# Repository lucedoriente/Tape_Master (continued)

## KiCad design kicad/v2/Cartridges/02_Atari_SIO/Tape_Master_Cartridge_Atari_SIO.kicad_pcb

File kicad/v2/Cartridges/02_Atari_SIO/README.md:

# Tape Master v2 — Cartuccia 02: Atari 8-Bit SIO Tape Interface

| Proprietà | Dettaglio / Valore |
| :--- | :--- |
| **Progetto** | Tape Master Exerciser & Signal Digitizer v2 |
| **Modulo** | Cartuccia Espansione #02 — Atari SIO (`02_Atari_SIO`) |
| **Piattaforme Compatibili** | Atari 400, 800, 800XL, 65XE, 130XE, XEGS, XE Game System |
| **Periferiche Supportate** | Atari 410, 1010, XC11, XC12, CA-12, XCA12, XC13, registratori compatibili Turbo (KSO, Silesia, Turbo 2000) |
| **Autore & Hardware Designer** | Alessio Iodice (`alessio67@gmail.com`) |
| **Data di Rilascio** | 2026-11-06 |
| **Revisione** | 2.0 (KiCad 9.0 Nativo) |
| **Licenza** | CC BY-NC-SA 4.0 |
| **Stato Validazione KiCad 9** | **0 Violazioni ERC / 0 Violazioni DRC / 0 Net Non Connesse / 0 Parity Issues** |

---

## 1. Descrizione Architetturale

La cartuccia **Cartuccia 02: Atari SIO** interfaccia il sistema **Tape Master v2** al bus seriale proprietario **Atari SIO (Serial Input/Output)** a 13 pin, utilizzato dall'intera famiglia di personal computer a 8-bit Atari (400, 800, serie XL, serie XE) per il pilotaggio dei registratori a cassette (modelli 410, 1010, XC11, XC12 e derivati con turbo tape).

### Caratteristiche Elettriche Chiave
1. **Trasmissione Dati Asincrona SIO (DATA IN - Pin 3)**:
   - La linea `DATA IN` dell'Atari opera a 600 baud (standard Atari FSK audio demodulato) o a bitrate superiori (sistemi Turbo fino a $4800\text{ baud}$).
   - Pilotata tramite doppio stadio invertitore Open-Collector ad alta velocità **74HCT06** (`U2`), con resistenza di pull-up locale da $1\text{ k}\Omega$ verso `+5V_SIO` (host console) e resistenza di pull-up da $10\text{ k}\Omega$ sull'ingresso logico collegato alla Mainboard.
2. **Ricezione Dati (DATA OUT - Pin 5)**:
   - Traslazione di livello da 5V a 3.0V tramite partitore resistivo di precisione ($R_1 = 2.2\text{ k}\Omega$, $R_2 = 3.3\text{ k}\Omega$) con clamp a doppio diodo Schottky a commutazione ultra-rapida **BAT54S** (`D2`) verso `+3.3V` e `GND`, proteggendo l'ingresso MCU `TAPE_REC_IN`.
3. **Controllo & Rilevamento Motore (MOTOR - Pin 8)**:
   - L'Atari attiva il motore tirando la linea a livello logico basso / massa (transistor open-collector sul computer).
   - Resistenza di pull-up da $10\text{ k}\Omega$ (`R3`) verso `+5V_SIO`, partitore $2.2\text{ k}\Omega / 3.3\text{ k}\Omega$ (`R4`, `R5`) e clamp Schottky **BAT54S** (`D4`) verso la linea `MOTOR_SENSE` della scheda madre.
4. **Acquisizione Audio / Traccia Stereo Ingest (AUDIO IN - Pin 11)**:
   - Il bus SIO prevede sul Pin 11 una traccia audio ausiliaria (usata nei nastri didattici Atari per audio parlato o musica mentre la traccia dati viene caricata in RAM).
   - Circuito di condizionamento dedicato con condensatore di disaccoppiamento DC da $4.7\ \mu\text{F}$ (`C3`), filtro passa-basso RC passivo ($R_6 = 1\text{ k}\Omega$, $C_4 = 10\text{ nF}$, frequenza di taglio $f_c \approx 15.9\text{ kHz}$) e resistenza di carico shunt da $10\text{ k}\Omega$ (`R7`), inviata alla linea `AUDIO_RAW_L` per il campionamento ADC / digitalizzazione stereo.
5. **Protezione ESD / Transitori**:
   - Array di soppressione TVS a bassa capacità parassita **USBLC6-2SC6** (`D1`) su tutte e 4 le linee esposte (`SIO_DATA_IN`, `SIO_DATA_OUT`, `SIO_MOTOR`, `SIO_AUDIO_IN`).
6. **Smart Plug & Play (Auto-ID Cartridge)**:
   - EEPROM I2C **24C02** (`U1`) configurata all'indirizzo `0x51` (`A0=1, A1=0, A2=0`), contenente il descrittore hardware con magic byte, revisione, pinout e parametri di campionamento.
   - Pin 26 del connettore bus principale `CART_DETECT_N` collegato a massa per rilevamento hardware automatico dell'inserimento scheda.
7. **Monitor Alimentazione Atari Console**:
   - Micro-LED verde 0805 `D3` (`+5V_SIO_OK`) con resistenza di zavorra da $1.5\text{ k}\Omega$ (`R10`), unico LED ammesso sulla cartuccia come da regole di progetto per visualizzare a colpo d'occhio la presenza dell'alimentazione erogata dalla console vintage.

---

## 2. Centralizzazione Diagnostica sul Front Panel (Daughterboard)

Come prescritto dalle regole ufficiali di progetto `tape-master-rules.md`, l'intera interfaccia diagnostica e di stato per l'operatore è centralizzata sul pannello frontale (`Tape_Master_UI_Panel`), evitando LED duplicati non visibili a banco.

I 5 LED diagnostici standardizzati sul pannello operatore riflettono il funzionamento della cartuccia Atari SIO:

| Riferimento UI | Colore | Serigrafia Standard | Segnale Mappato per Atari SIO | Funzione Operativa |
| :---: | :---: | :---: | :--- | :--- |
| **D2** | Verde | **`PLAY`** | `SIO_DATA_IN` (Pin 3) | Trasmissione dati dal Tape Master verso la console Atari (emulazione nastro CAS / dump) |
| **D3** | Rosso | **`REC`** | `SIO_DATA_OUT` (Pin 5) | Ricezione dati e salvataggio dump dal computer Atari verso il Tape Master |
| **D4** | Giallo | **`MOTOR`** | `SIO_MOTOR` (Pin 8) | Linea motore abilitata dall'Atari (computer in attesa di caricamento o salvataggio) |
| **D5** | Blu | **`SIGNAL`** | `SIO_AUDIO_IN` (Pin 11) | Presenza traccia audio analogica / sincronismo portante SIO / turbo pulse |
| **D6** | Verde | **`PWR`** | Alimentazione Tape Master | Alimentazione principale di sistema attiva e MCU operativo |
| **D10..D19** | 8V/1G/1R | **`AZIMUTH / VU-METER`** | Livello di picco ADC `AUDIO_RAW_L` | Barra VU-meter per regolazione azimut / livello volume traccia parlato |

---

## 3. Doppia Connettività Esterna

La cartuccia adotta la configurazione a **doppia porta**:
1. **`J2` — Presa Femmina Proprietaria Atari SIO 13-Pin**: Connettore a guscio originale per l'inserimento diretto del cavo SIO standard proveniente dal computer o dal registratore.
2. **`J3` — Pin-Header Maschio Breakout 1x13 passo 2.54 mm**: Pin header montato a bordo scheda con serigrafia esplicita di ciascun pin, ideale per test a banco, oscilloscopio, analizzatore logico o cablaggi rapidi.

### Piedinatura Connettori SIO (`J2` e `J3`)

| Pin # | Segnale SIO | Connessione su Cartuccia | Direzione | Descrizione |
| :---: | :--- | :--- | :---: | :--- |
| **1** | `CLK_I` (Clock In) | Header Breakout `J3` / `J2` | Ingresso Atari | Segnale di clock esterno per periferiche sincrone |
| **2** | `CLK_O` (Clock Out) | Header Breakout `J3` / `J2` | Uscita Atari | Clock generato dalla CPU/POKEY |
| **3** | `DATA_IN` | Buffer Open-Collector `74HCT06` | Ingresso Atari | Ricezione seriale dati dal registratore (600+ baud) |
| **4** | `GND` | Piano di Massa Scheda (`GND`) | Riferimento | Massa logica e potenza |
| **5** | `DATA_OUT` | Partitore $2.2\text{k}/3.3\text{k}$ $\rightarrow$ `TAPE_REC_IN` | Uscita Atari | Dati seriali trasmessi dalla console verso la cassetta |
| **6** | `GND` | Piano di Massa Scheda (`GND`) | Riferimento | Massa logica e potenza |
| **7** | `COMMAND` | Pull-up $10\text{ k}\Omega$ $\rightarrow$ Header Breakout `J3` | Uscita Atari | Linea di comando attiva bassa (abilitazione bus per disk drive) |
| **8** | `MOTOR` | Pull-up + Partitore $\rightarrow$ `MOTOR_SENSE` | Uscita Atari | Controllo motore registratore (attivo a 0V) |
| **9** | `PROCEED` | Header Breakout `J3` / `J2` | Ingresso Atari | Linea di interrupt / handshake periferiche |
| **10** | `+5V_SIO` | Monitor LED `D3` & Pull-up buffer | Uscita Atari | Tensione +5V erogata dall'Atari (max $100\text{ mA}$) |
| **11** | `AUDIO_IN` | Filtro passa-basso $15.9\text{ kHz}$ $\rightarrow$ `AUDIO_RAW_L` | Ingresso Atari | Traccia audio analogica ausiliaria cassetta |
| **12** | `+12V` | Header Breakout `J3` / `J2` | Non connesso | Presente solo su Atari 400/800 per alimentatori d'epoca |
| **13** | `INTERRUPT` | Header Breakout `J3` / `J2` | Ingresso Atari | Linea di richiesta interruzione al computer |

---

## 4. Specifiche Meccaniche e Bordo Scheda

- **Dimensioni**: $74.00\text{ mm} \times 55.00\text{ mm}$.
- **Intagli Meccanici**: Due intagli su `Edge.Cuts` ($6.0\text{ mm} \times 8.0\text{ mm}$) per l'alloggiamento delle leve di ritenuta del connettore `J1` della Mainboard.
- **Complanarità**: Connettore maschio ad angolo retto sulla Mainboard e connettore femmina ad angolo retto sulla Cartuccia (`J1`) permettono alle due schede di rimanere **perfettamente parallele e complanari**, con la cartuccia che estende orizzontalmente all'indietro il corpo principale del Tape Master.

---

## 5. File di Rilascio e Produzione

- Schema Elettrico KiCad: `Tape_Master_Cartridge_Atari_SIO.kicad_sch`
- Layout PCB KiCad: `Tape_Master_Cartridge_Atari_SIO.kicad_pcb`
- Modello 3D Meccanico Solido PCB Assemblato: `Tape_Master_Cartridge_Atari_SIO.step`
- Schema Elettrico Vettoriale: `Tape_Master_Cartridge_Atari_SIO.pdf` e `Tape_Master_Cartridge_Atari_SIO_Sch.svg`
- Disegno PCB Top Layer: `Tape_Master_Cartridge_Atari_SIO_Top.pdf` e `Tape_Master_Cartridge_Atari_SIO_Top.svg`
- Disegno PCB Bottom Layer: `Tape_Master_Cartridge_Atari_SIO_Bottom.pdf`
- Report Collaudo ERC: `Tape_Master_Cartridge_Atari_SIO-erc.rpt` (0 errori, 0 warning)
- Report Collaudo DRC: `Tape_Master_Cartridge_Atari_SIO-drc.rpt` (0 errori, 0 warning, 0 unconnected, 0 parity issues)

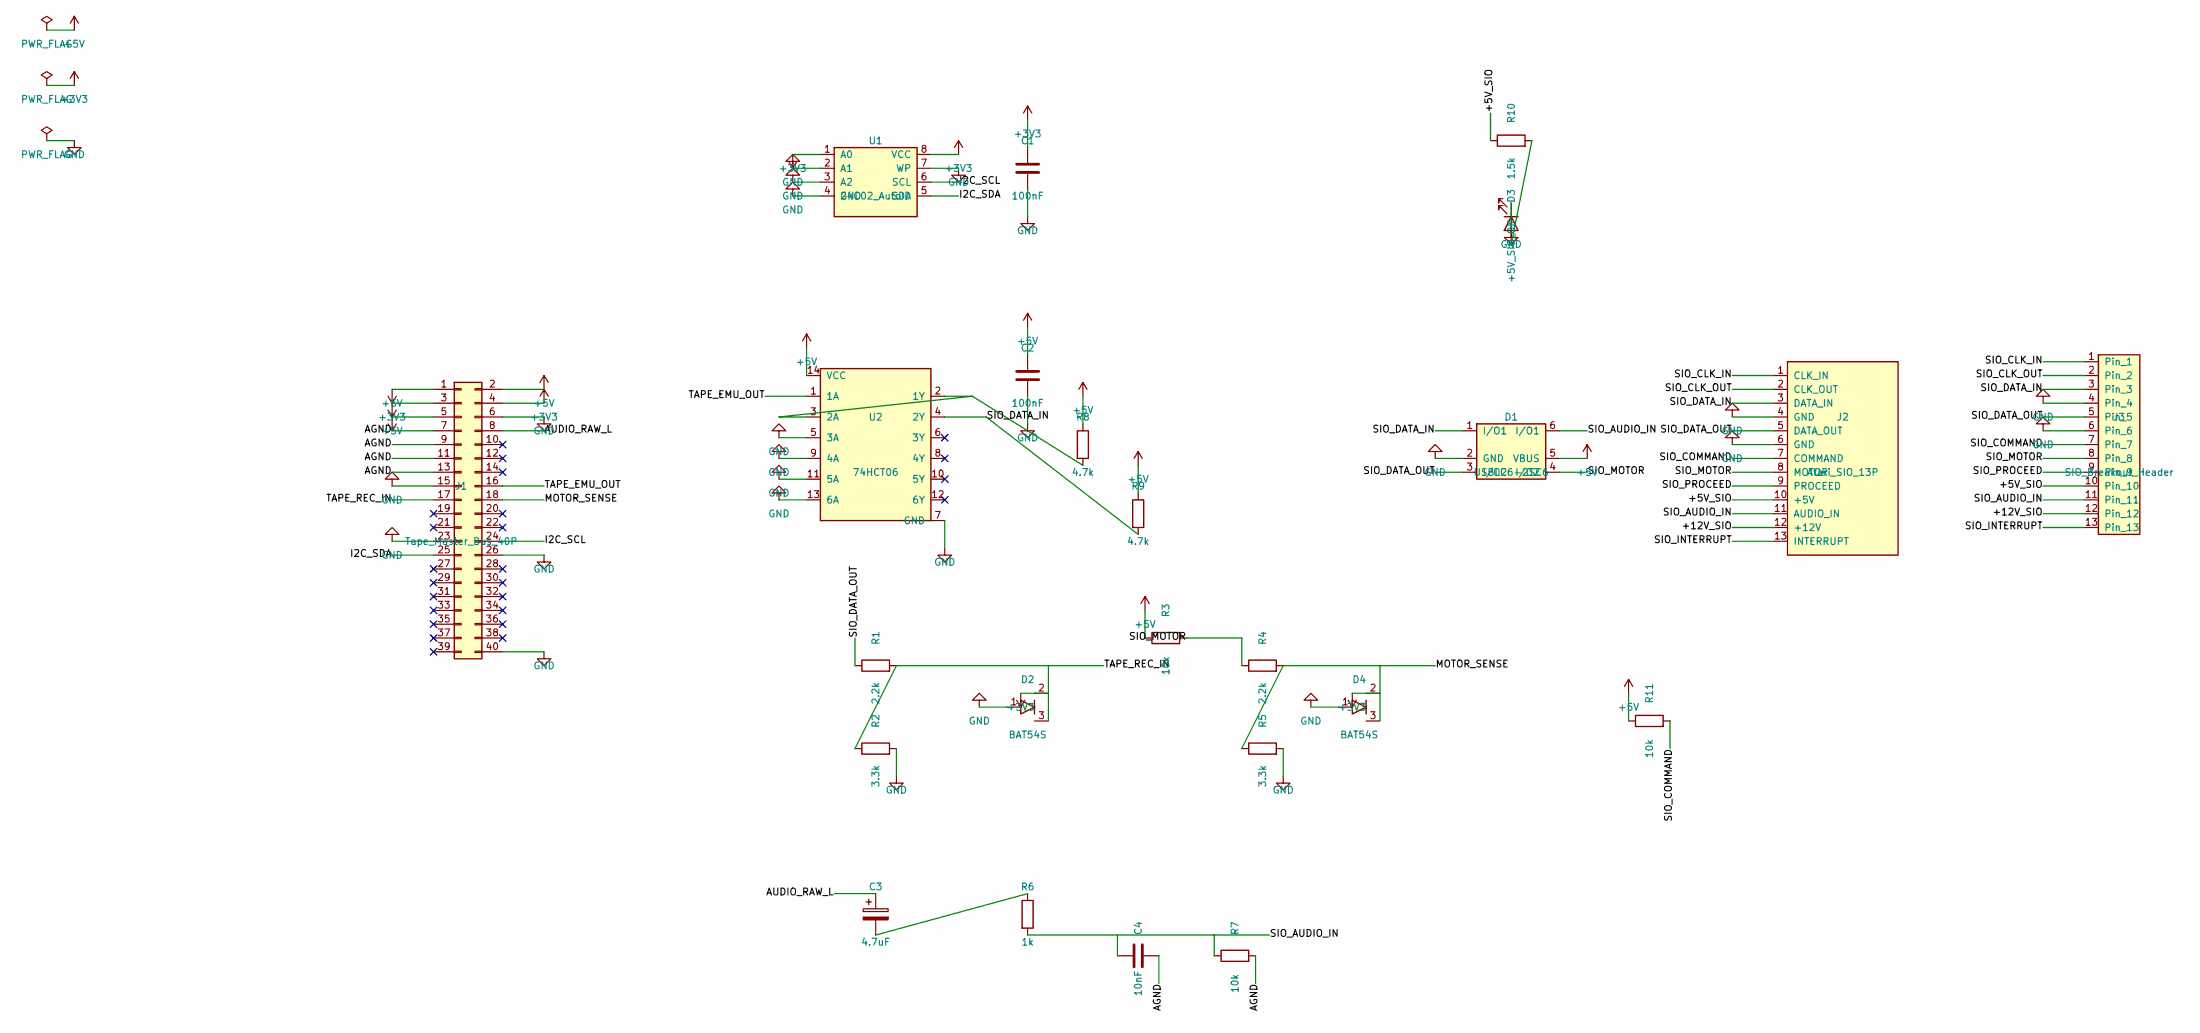
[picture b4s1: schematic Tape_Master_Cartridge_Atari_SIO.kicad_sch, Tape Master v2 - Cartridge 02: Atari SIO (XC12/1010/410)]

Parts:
C1, C2: 100nF; C_0805_2012Metric
C3: 4.7uF; CP_Elec_5x5.4
C4: 10nF; C_0805_2012Metric
D1: USBLC6-2SC6; SOT-23-6
D2, D4: BAT54S; SOT-23
D3: +5V_SIO_OK; LED_0805_2012Metric
J1: Tape_Master_Bus_40P; PinSocket_2x20_P2.54mm_Horizontal_Cartridge
J2: Atari_SIO_13P
J3: SIO_Breakout_Header; PinHeader_1x13_P2.54mm_Vertical
R1, R4: 2.2k; R_0805_2012Metric
R2, R5: 3.3k; R_0805_2012Metric
R3, R7, R11: 10k; R_0805_2012Metric
R6: 1k; R_0805_2012Metric
R8, R9: 4.7k; R_0805_2012Metric
R10: 1.5k; R_0805_2012Metric
U1: 24C02_AutoID; SOIC-8_3.9x4.9mm_P1.27mm
U2: 74HCT06; SOIC-14_3.9x8.7mm_P1.27mm

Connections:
+3V3: C1.1, D2.2 (C2), D4.2 (C2), J1.3, J1.4, U1.1 (A0), U1.8 (VCC)
+5V: C2.1, D1.5 (VBUS), J1.1, J1.2, J1.5, R3.1, R8.1, R9.1, R11.1, U2.14 (VCC)
/+5V_SIO: J2.10 (+5V), J3.10, R10.1
/+12V_SIO: J2.12 (+12V), J3.12
/AGND: C4.2, J1.7, J1.9, J1.11, J1.13, R7.2
/AUDIO_RAW_L: C3.1, J1.8
/I2C_SCL: J1.24, U1.6 (SCL)
/I2C_SDA: J1.25, U1.5 (SDA)
/MOTOR_SENSE: D4.3 (C1A2), J1.18, R4.2, R5.1
/SIO_AUDIO_IN: C4.1, D1.6 (I/O1), J2.11 (AUDIO_IN), J3.11, R6.2, R7.1
/SIO_CLK_IN: J2.1 (CLK_IN), J3.1
/SIO_CLK_OUT: J2.2 (CLK_OUT), J3.2
/SIO_COMMAND: J2.7 (COMMAND), J3.7, R11.2
/SIO_DATA_IN: D1.1 (I/O1), J2.3 (DATA_IN), J3.3, R9.2, U2.4 (2Y)
/SIO_DATA_OUT: D1.3 (I/O2), J2.5 (DATA_OUT), J3.5, R1.1
/SIO_INTERRUPT: J2.13 (INTERRUPT), J3.13
/SIO_MOTOR: D1.4 (I/O2), J2.8 (MOTOR), J3.8, R3.2, R4.1
/SIO_PROCEED: J2.9 (PROCEED), J3.9
/TAPE_EMU_OUT: J1.16, U2.1 (1A)
/TAPE_REC_IN: D2.3 (C1A2), J1.17, R1.2, R2.1
GND: C1.2, C2.2, D1.2 (GND), D2.1 (A1), D3.1 (K), D4.1 (A1), J1.6, J1.15, J1.23, J1.26, J1.40, J2.4 (GND), J2.6 (GND), J3.4, J3.6, R2.2, R5.2, U1.2 (A1), U1.3 (A2), U1.4 (GND), U1.7 (WP), U2.5 (3A), U2.7 (GND), U2.9 (4A), U2.11 (5A), U2.13 (6A)
unnamed: C3.2, R6.1
unnamed: D3.2 (A), R10.2
unnamed: R8.2, U2.2 (1Y), U2.3 (2A)

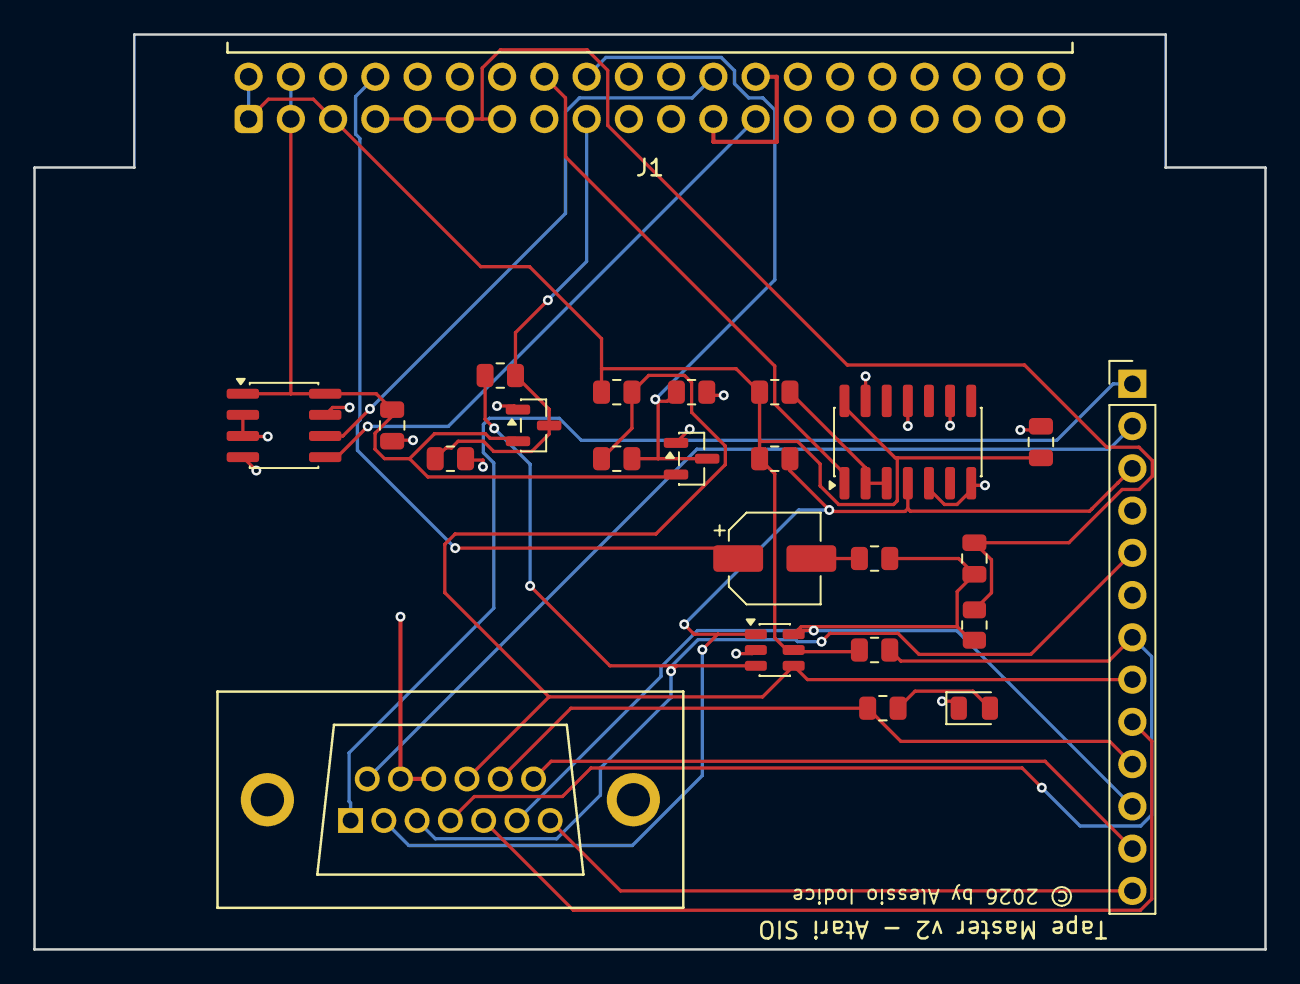
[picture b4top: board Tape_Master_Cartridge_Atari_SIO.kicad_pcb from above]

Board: 2 copper layers, 74.0 x 55.0 mm, 24 parts (0 on the bottom side), 24 nets.

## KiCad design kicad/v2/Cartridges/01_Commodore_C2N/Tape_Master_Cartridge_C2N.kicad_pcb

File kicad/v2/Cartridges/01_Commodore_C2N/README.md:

# Tape Master v2 - Cartuccia 01: Commodore C2N Datassette (PET / VIC-20 / C64 / C128 / C16)

| Proprietà | Dettaglio / Valore |
| :--- | :--- |
| **Progetto** | Tape Master Exerciser & Signal Digitizer v2 |
| **Modulo** | Cartuccia Espansione #01 - Commodore C2N Datassette (`01_Commodore_C2N`) |
| **Piattaforme Compatibili** | Commodore PET 2001/3000/4000/8000, VIC-20, Commodore 64, Commodore 128, Commodore 16, Plus/4 (con adattatore mini-DIN standard) |
| **Periferiche Supportate** | Datassette Commodore 1530 / 1531, cavi di prolunga per registratore originale a cassetta |
| **Autore & Hardware Designer** | Alessio Iodice (`alessio67@gmail.com`) |
| **Data di Rilascio** | 2026-11-06 |
| **Revisione** | 2.0 (KiCad 9.0 Nativo) |
| **Licenza** | CC BY-NC-SA 4.0 |
| **Stato Validazione KiCad 9** | **0 Violazioni ERC / 0 Violazioni DRC / 0 Net Non Connesse / 0 Parity Issues** |

---

## 1. Descrizione Architetturale

La **Cartuccia 01: Commodore C2N Datassette** interfaccia il sistema **Tape Master v2** al bus a cassetta proprietario Commodore (*Cassette Port*).
Il bus Commodore a 6 pin presenta un'interfaccia edge-connector con segnali logici digitali TTL a 5V:
- `GND` (Pin A-1 / B-1)
- `+5V` (Pin A-2 / B-2)
- `MOTOR` (Pin A-3 / B-3): Alimentazione del motore (9V/6V switched da computer)
- `READ` (Pin A-4 / B-4): Segnale dati in lettura verso il computer
- `WRITE` (Pin A-5 / B-5): Segnale dati in scrittura dal computer
- `SENSE` (Pin A-6 / B-6): Rilevamento pressione tasti Play/Record/Rew/FF

Il modulo cartuccia integra:
1. Connettore Card-Edge maschio sagomato su PCB (`J2`) con smussatura a 45° per innesto diretto nella porta cassetta del computer Commodore.
2. Connettore a pettine femmina (`J3`) per il collegamento passante di un vero registratore Commodore 1530 a scopo di sniffer/analizzatore.
3. Buffer open-collector ad alta velocità 74HCT06 per il pilotaggio della linea `READ`.
4. Condizionatori di livello e protezioni TVS/clamping Schottky per `WRITE`, `MOTOR` e `SENSE`.
5. EEPROM I2C 24C02 per Auto-ID Smart Plug & Play.

---

## 2. Centralizzazione Diagnostica sul Front Panel (Daughterboard)

Conformemente alle regole di progetto `tape-master-rules.md`, tutti i LED diagnostici sono centralizzati sull'UI Panel:
- **D2 (`PLAY`)**: Linea `READ` attiva verso il computer Commodore.
- **D3 (`REC`)**: Linea `WRITE` attiva proveniente dal computer Commodore.
- **D4 (`MOTOR`)**: Tensione motore abilitata dal computer.
- **D5 (`SIGNAL`)**: Feedback `SENSE` / impulsi di clock.
- **D6 (`PWR`)**: Alimentazione di sistema attiva.
- **D10..D19**: VU-meter analogico / regolazione azimut testina.

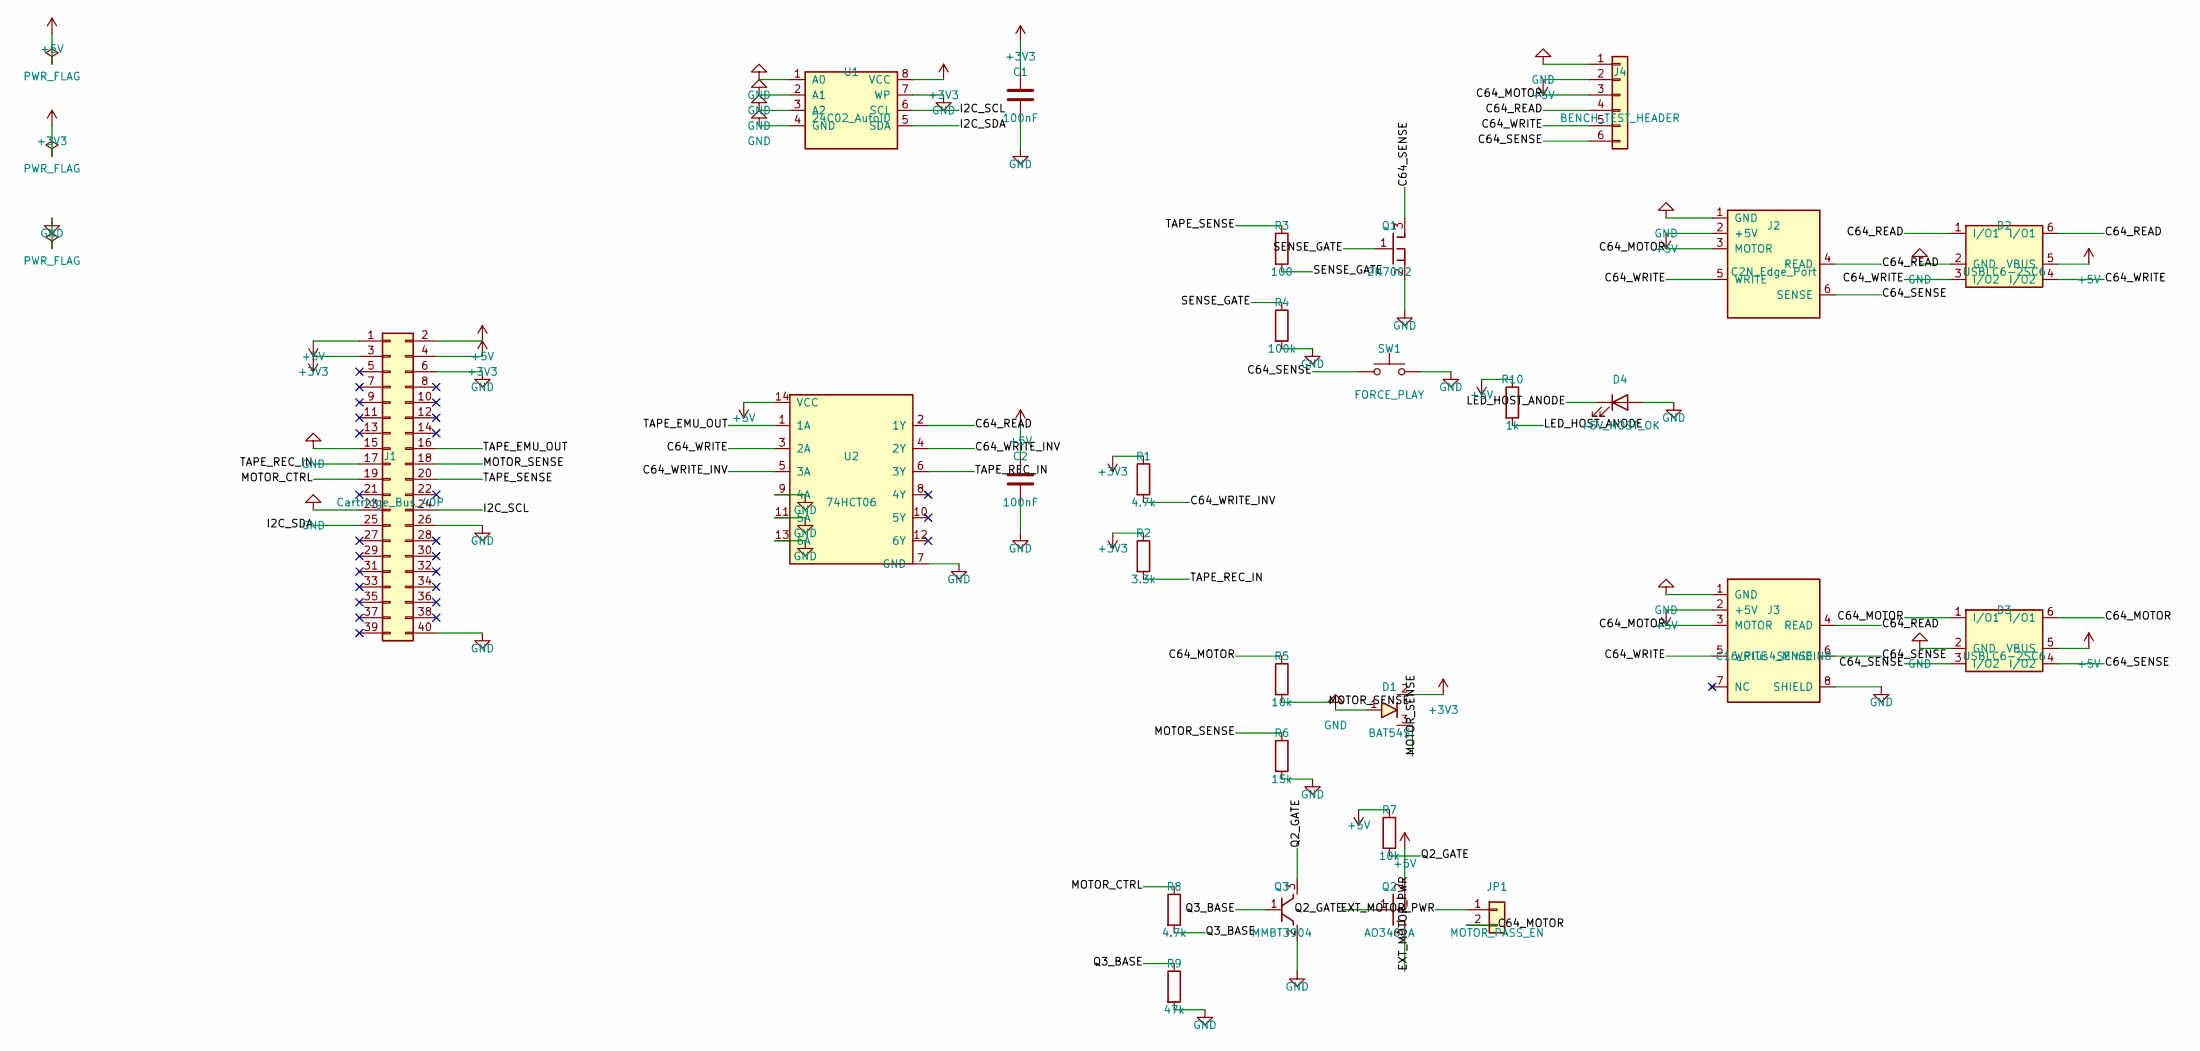
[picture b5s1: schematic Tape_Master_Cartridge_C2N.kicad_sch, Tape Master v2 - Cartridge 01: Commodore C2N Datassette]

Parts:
C1, C2: 100nF; C_0805_2012Metric
D1: BAT54S; SOT-23
D2, D3: USBLC6-2SC6; SOT-23-6
D4: +5V_HOST_OK; LED_0805_2012Metric
J1: Cartridge_Bus_40P; PinSocket_2x20_P2.54mm_Horizontal_Cartridge
J2: C2N_Edge_Port; C2N_Edge_Connector
J3: C16_Plus4_MiniDIN8; Mini-DIN-8_MD-80_Horizontal
J4: BENCH_TEST_HEADER; PinHeader_1x06_P2.54mm_Vertical
JP1: MOTOR_PASS_EN; PinHeader_1x02_P2.54mm_Vertical
Q1: 2N7002; SOT-23
Q2: AO3401A; SOT-23
Q3: MMBT3904; SOT-23
R1, R8: 4.7k; R_0805_2012Metric
R2: 3.3k; R_0805_2012Metric
R3: 100; R_0805_2012Metric
R4: 100k; R_0805_2012Metric
R5, R7: 10k; R_0805_2012Metric
R6: 15k; R_0805_2012Metric
R9: 47k; R_0805_2012Metric
R10: 1k; R_0805_2012Metric
SW1: FORCE_PLAY; SW_SPST_PTS645
U1: 24C02_AutoID; SOIC-8_3.9x4.9mm_P1.27mm
U2: 74HCT06; SOIC-14_3.9x8.7mm_P1.27mm

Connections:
+3V3: C1.1, D1.2 (C2), J1.3, J1.4, R1.1, R2.1, U1.8 (VCC)
+5V: C2.1, D2.5 (VBUS), D3.5 (VBUS), J1.1, J1.2, J2.2 (+5V), J3.2 (+5V), J4.2, Q2.2 (S), R7.1, R10.1, U2.14 (VCC)
/C64_MOTOR: D3.1 (I/O1), D3.6 (I/O1), J2.3 (MOTOR), J3.3 (MOTOR), J4.3, JP1.2, R5.1
/C64_READ: D2.1 (I/O1), D2.6 (I/O1), J2.4 (READ), J3.4 (READ), J4.4, U2.2 (1Y)
/C64_SENSE: D3.3 (I/O2), D3.4 (I/O2), J2.6 (SENSE), J3.6 (SENSE), J4.6, Q1.3 (D), SW1.1
/C64_WRITE: D2.3 (I/O2), D2.4 (I/O2), J2.5 (WRITE), J3.5 (WRITE), J4.5, U2.3 (2A)
/C64_WRITE_INV: R1.2, U2.4 (2Y), U2.5 (3A)
/EXT_MOTOR_PWR: JP1.1, Q2.3 (D)
/I2C_SCL: J1.24, U1.6 (SCL)
/I2C_SDA: J1.25, U1.5 (SDA)
/LED_HOST_ANODE: D4.1 (K), R10.2
/MOTOR_CTRL: J1.19, R8.1
/MOTOR_SENSE: D1.3 (C1A2), J1.18, R5.2, R6.1
/Q2_GATE: Q2.1 (G), Q3.3 (C), R7.2
/Q3_BASE: Q3.1 (B), R8.2, R9.1
/SENSE_GATE: Q1.1 (G), R3.2, R4.1
/TAPE_EMU_OUT: J1.16, U2.1 (1A)
/TAPE_REC_IN: J1.17, R2.2, U2.6 (3Y)
/TAPE_SENSE: J1.20, R3.1
GND: C1.2, C2.2, D1.1 (A1), D2.2 (GND), D3.2 (GND), D4.2 (A), J1.6, J1.15, J1.23, J1.26, J1.40, J2.1 (GND), J3.1 (GND), J3.8 (SHIELD), J4.1, Q1.2 (S), Q3.2 (E), R4.2, R6.2, R9.2, SW1.2, U1.1 (A0), U1.2 (A1), U1.3 (A2), U1.4 (GND), U1.7 (WP), U2.7 (GND), U2.9 (4A), U2.11 (5A), U2.13 (6A)

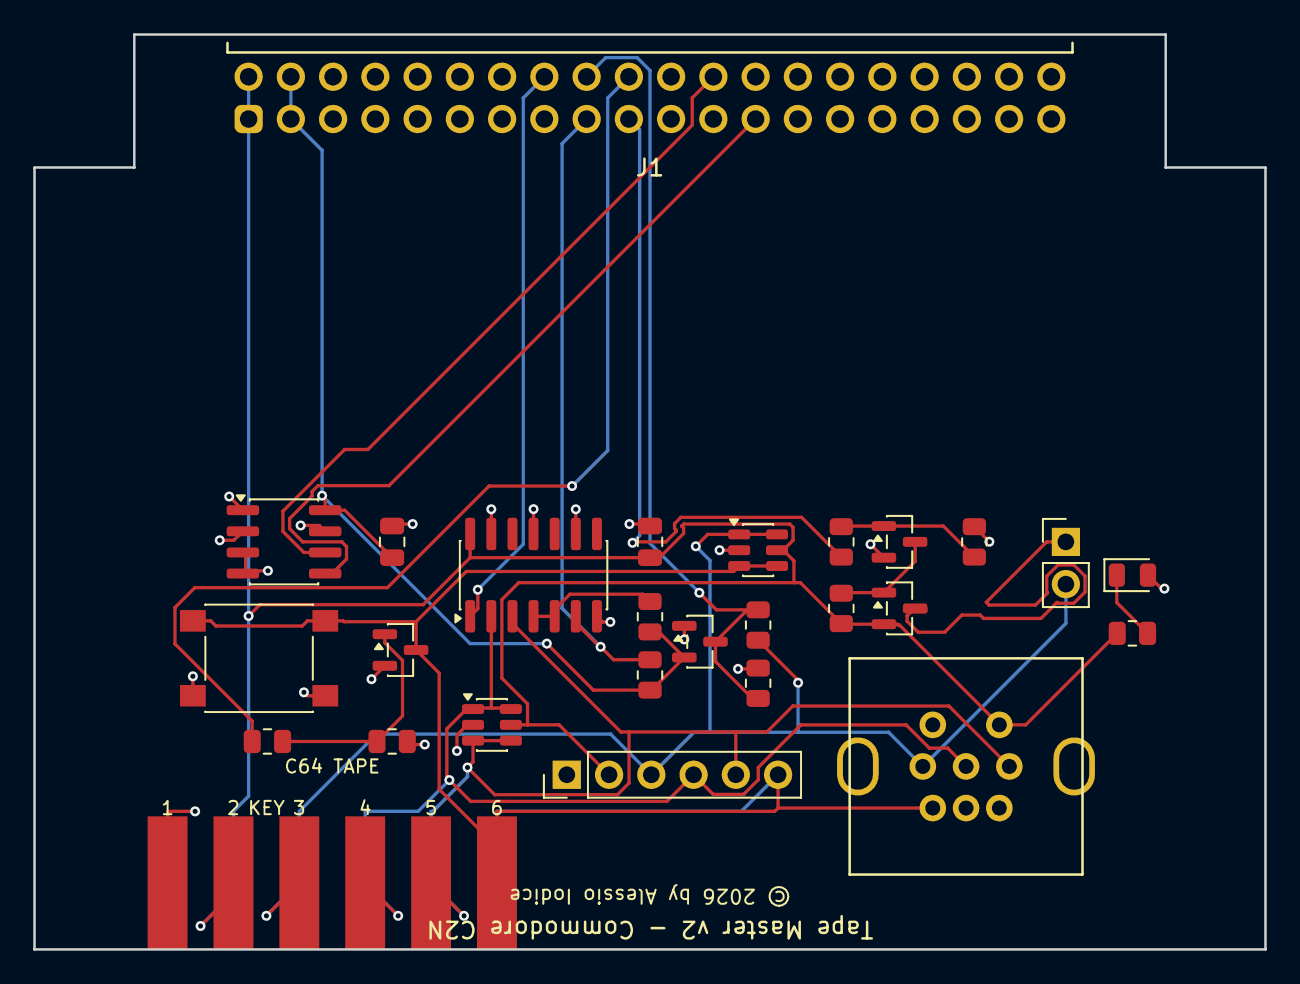
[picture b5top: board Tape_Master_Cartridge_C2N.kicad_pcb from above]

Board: 2 copper layers, 74.0 x 55.0 mm, 27 parts (0 on the bottom side), 20 nets.

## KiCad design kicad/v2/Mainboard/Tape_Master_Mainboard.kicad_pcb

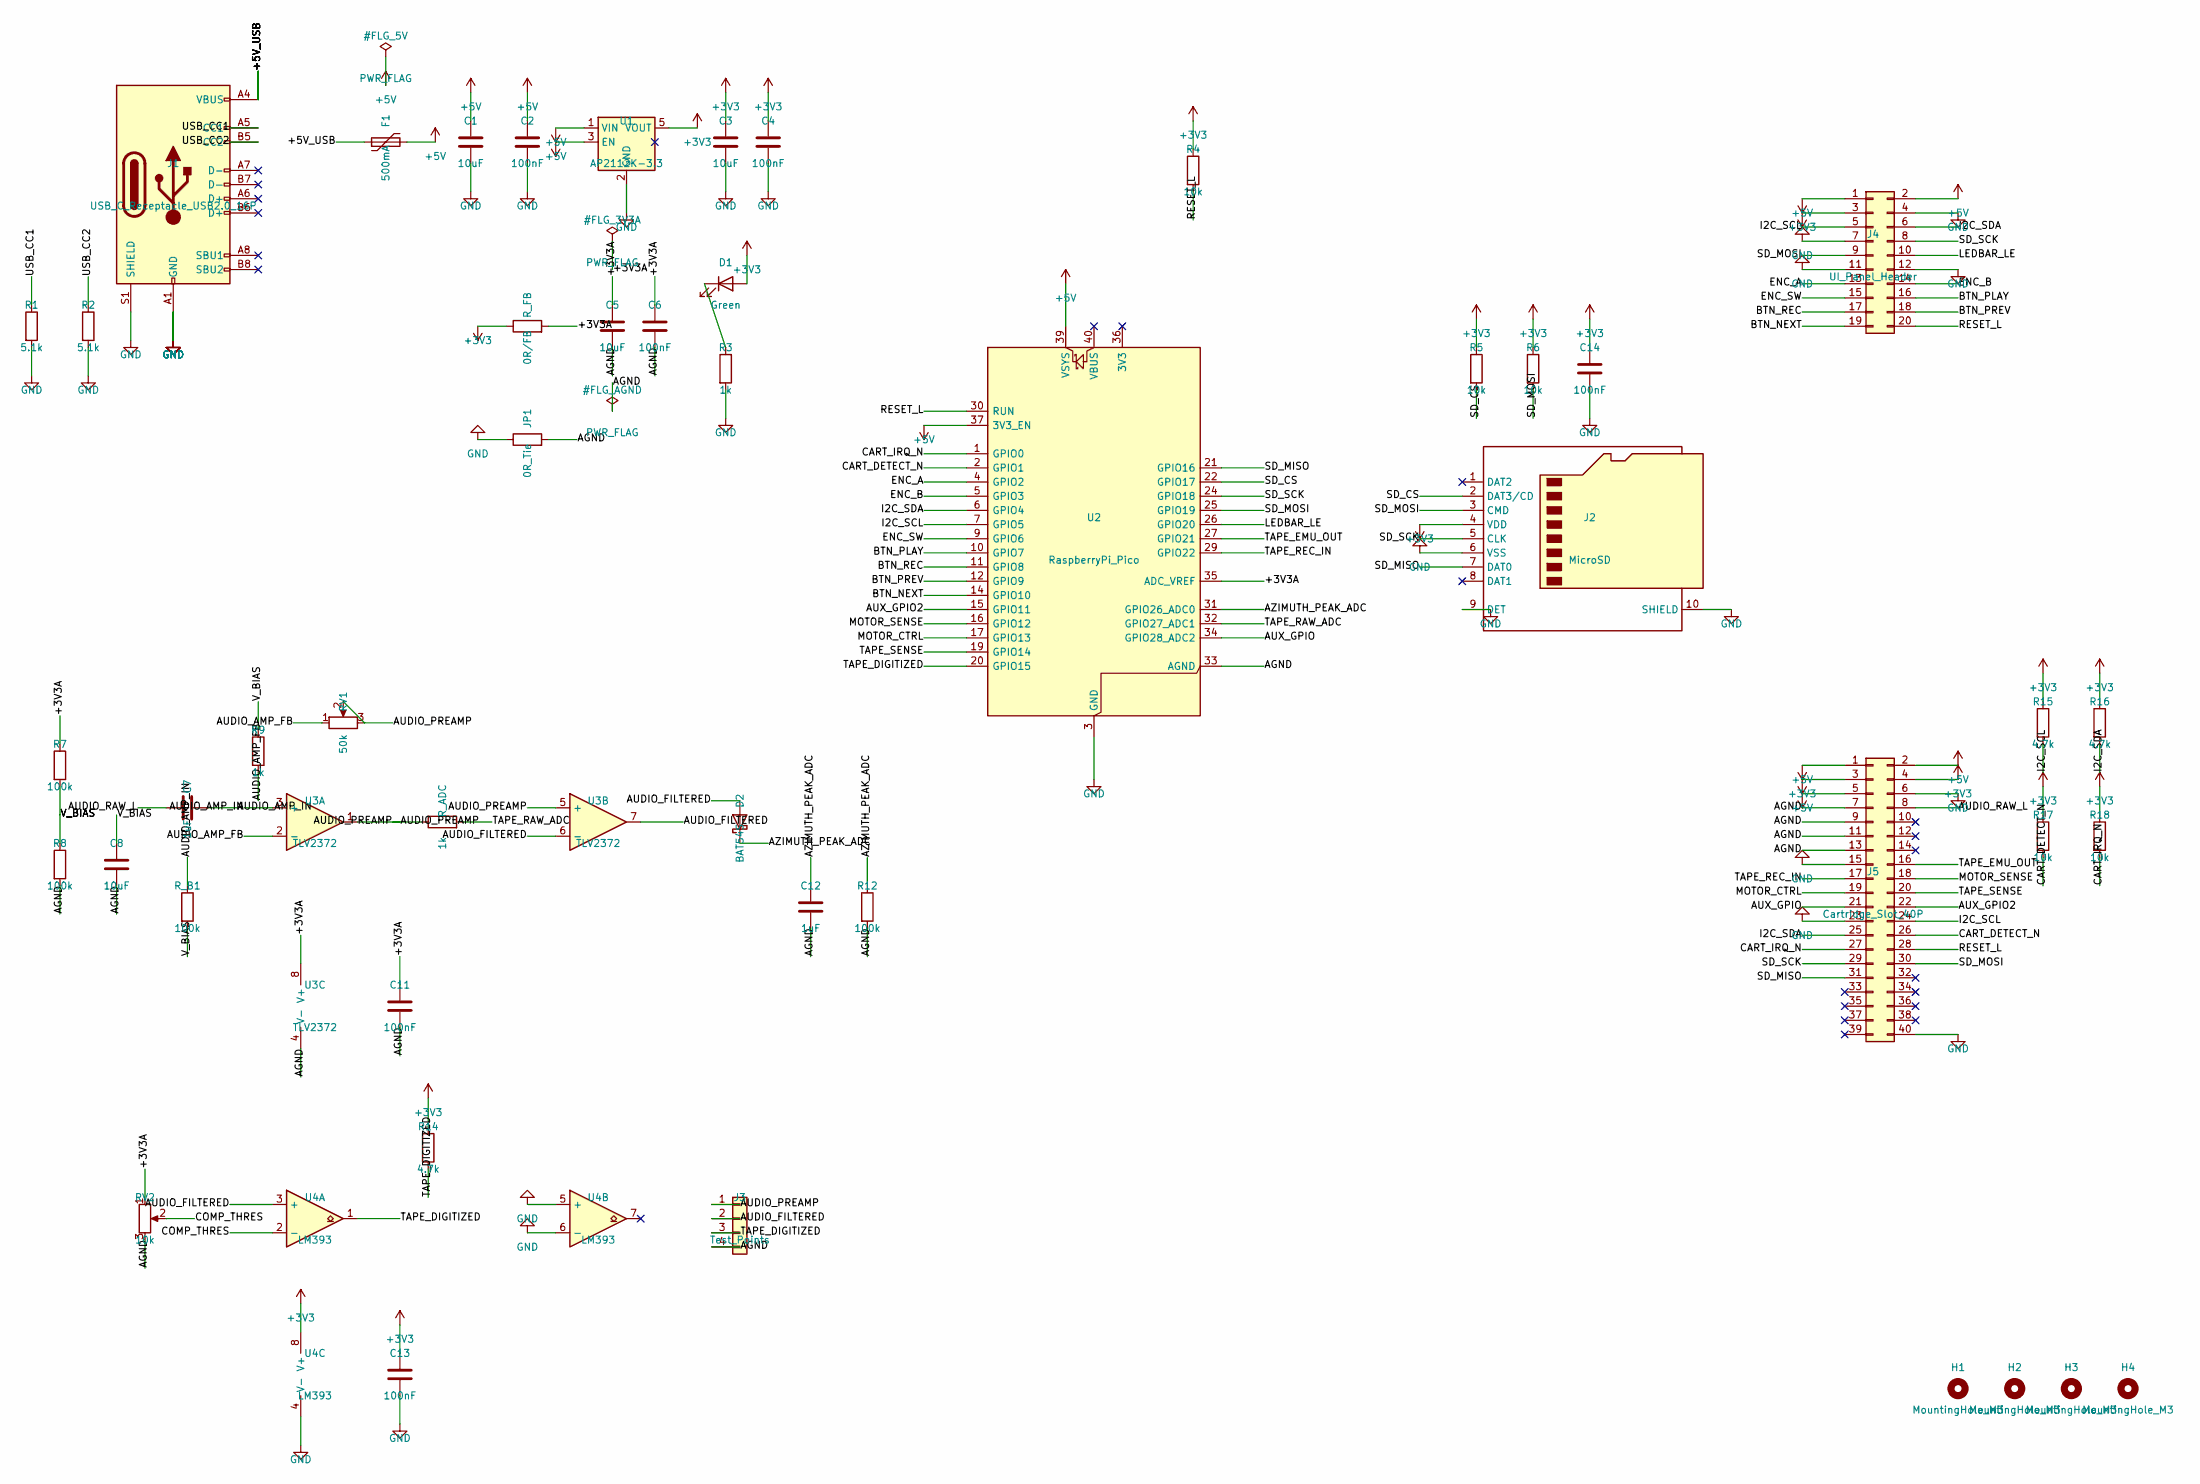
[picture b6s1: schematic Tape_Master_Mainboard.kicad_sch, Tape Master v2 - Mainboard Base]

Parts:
C1, C3, C5, C8: 10uF; C_0805_2012Metric
C2, C4, C6, C11, C13, C14: 100nF; C_0805_2012Metric
C7, C12: 1uF; C_0805_2012Metric
D1: Green; LED_0805_2012Metric
D2: BAT54S; SOT-23
F1: 500mA; Fuse_1206_3216Metric
H1, H2, H3, H4: MountingHole_M3; MountingHole_3.2mm_M3
J1: USB_C_Receptacle_USB2.0_16P; USB_C_Receptacle_GCT_USB4105-xx-A_16P_TopMnt_Horizontal
J2: MicroSD; microSD_HC_Hirose_DM3D-SF
J3: Test_Points; PinHeader_1x04_P2.54mm_Vertical
J4: UI_Panel_Header; IDC-Header_2x10_P2.54mm_Vertical
J5: Cartridge_Slot_40P; IDC-Header_2x20_P2.54mm_Horizontal
JP1: 0R_Tie; R_0805_2012Metric
R1, R2: 5.1k; R_0805_2012Metric
R3, R9: 1k; R_0805_2012Metric
R4, R5, R6, R17, R18: 10k; R_0805_2012Metric
R7, R8, R12: 100k; R_0805_2012Metric
R14, R15, R16: 4.7k; R_0805_2012Metric
RV1: 50k; Potentiometer_Bourns_3296W_Vertical
RV2: 10k; Potentiometer_Bourns_3296W_Vertical
R_ADC: 1k; R_0805_2012Metric
R_B1: 100k; R_0805_2012Metric
R_FB: 0R/FB; R_0805_2012Metric
U1: AP2112K-3.3; SOT-23-5
U2: RaspberryPi_Pico; RaspberryPi_Pico_Common_THT
U3: TLV2372; SOIC-8_3.9x4.9mm_P1.27mm
U4: LM393; SOIC-8_3.9x4.9mm_P1.27mm

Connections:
+3V3: C3.1, C4.1, C13.1, C14.1, D1.2 (A), J2.4 (VDD), J4.3, J5.3, J5.4, R4.1, R5.1, R6.1, R14.1, R15.1, R16.1, R17.1, R18.1, R_FB.1, U1.5 (VOUT), U4.8 (V+)
+5V: C1.1, C2.1, F1.2, J4.1, J4.2, J5.1, J5.2, J5.5, U1.1 (VIN), U1.3 (EN), U2.37 (3V3_EN), U2.39 (VSYS)
/+3V3A: C5.1, C6.1, C11.1, R7.1, RV2.1, R_FB.2, U2.35 (ADC_VREF), U3.8 (V+)
/+5V_USB: F1.1, J1.A4 (VBUS), J1.A9 (VBUS), J1.B4 (VBUS), J1.B9 (VBUS)
/AGND: C5.2, C6.2, C8.2, C11.2, C12.2, J3.4, J5.7, J5.9, J5.11, J5.13, JP1.2, R8.2, R12.2, RV2.3, U2.33 (AGND), U3.4 (V-)
/AUDIO_AMP_FB: R9.2, RV1.1, U3.2 (-)
/AUDIO_AMP_IN: C7.2, R_B1.1, U3.3 (+)
/AUDIO_FILTERED: D2.2 (A), J3.2, U3.6 (-), U3.7, U4.3 (+)
/AUDIO_PREAMP: J3.1, RV1.2, RV1.3, R_ADC.1, U3.1, U3.5 (+)
/AUDIO_RAW_L: C7.1, J5.8
/AUX_GPIO: J5.21, U2.34 (GPIO28_ADC2)
/AUX_GPIO2: J5.22, U2.15 (GPIO11)
/AZIMUTH_PEAK_ADC: C12.1, D2.1 (K), R12.1, U2.31 (GPIO26_ADC0)
/BTN_NEXT: J4.19, U2.14 (GPIO10)
/BTN_PLAY: J4.16, U2.10 (GPIO7)
/BTN_PREV: J4.18, U2.12 (GPIO9)
/BTN_REC: J4.17, U2.11 (GPIO8)
/CART_DETECT_N: J5.26, R17.2, U2.2 (GPIO1)
/CART_IRQ_N: J5.27, R18.2, U2.1 (GPIO0)
/COMP_THRES: RV2.2, U4.2 (-)
/ENC_A: J4.13, U2.4 (GPIO2)
/ENC_B: J4.14, U2.5 (GPIO3)
/ENC_SW: J4.15, U2.9 (GPIO6)
/I2C_SCL: J4.5, J5.24, R15.2, U2.7 (GPIO5)
/I2C_SDA: J4.6, J5.25, R16.2, U2.6 (GPIO4)
/LEDBAR_LE: J4.10, U2.26 (GPIO20)
/MOTOR_CTRL: J5.19, U2.17 (GPIO13)
/MOTOR_SENSE: J5.18, U2.16 (GPIO12)
/RESET_L: J4.20, J5.28, R4.2, U2.30 (RUN)
/SD_CS: J2.2 (DAT3/CD), R5.2, U2.22 (GPIO17)
/SD_MISO: J2.7 (DAT0), J5.31, U2.21 (GPIO16)
/SD_MOSI: J2.3 (CMD), J4.9, J5.30, R6.2, U2.25 (GPIO19)
/SD_SCK: J2.5 (CLK), J4.8, J5.29, U2.24 (GPIO18)
/TAPE_DIGITIZED: J3.3, R14.2, U2.20 (GPIO15), U4.1
/TAPE_EMU_OUT: J5.16, U2.27 (GPIO21)
/TAPE_RAW_ADC: R_ADC.2, U2.32 (GPIO27_ADC1)
/TAPE_REC_IN: J5.17, U2.29 (GPIO22)
/TAPE_SENSE: J5.20, U2.19 (GPIO14)
/USB_CC1: J1.A5 (CC1), R1.1
/USB_CC2: J1.B5 (CC2), R2.1
/V_BIAS: C8.1, R7.2, R8.1, R9.1, R_B1.2
GND: C1.2, C2.2, C3.2, C4.2, C13.2, C14.2, J1.A1 (GND), J1.A12 (GND), J1.B1 (GND), J1.B12 (GND), J1.S1 (SHIELD), J2.6 (VSS), J2.9 (DET), J2.10 (SHIELD), J4.4, J4.7, J4.11, J4.12, J5.6, J5.15, J5.23, J5.40, JP1.1, R1.2, R2.2, R3.2, U1.2 (GND), U2.3 (GND), U2.8 (GND), U2.13 (GND), U2.18 (GND), U2.23 (GND), U2.28 (GND), U2.38 (GND), U4.4 (V-), U4.5 (+), U4.6 (-)
unnamed: D1.1 (K), R3.1

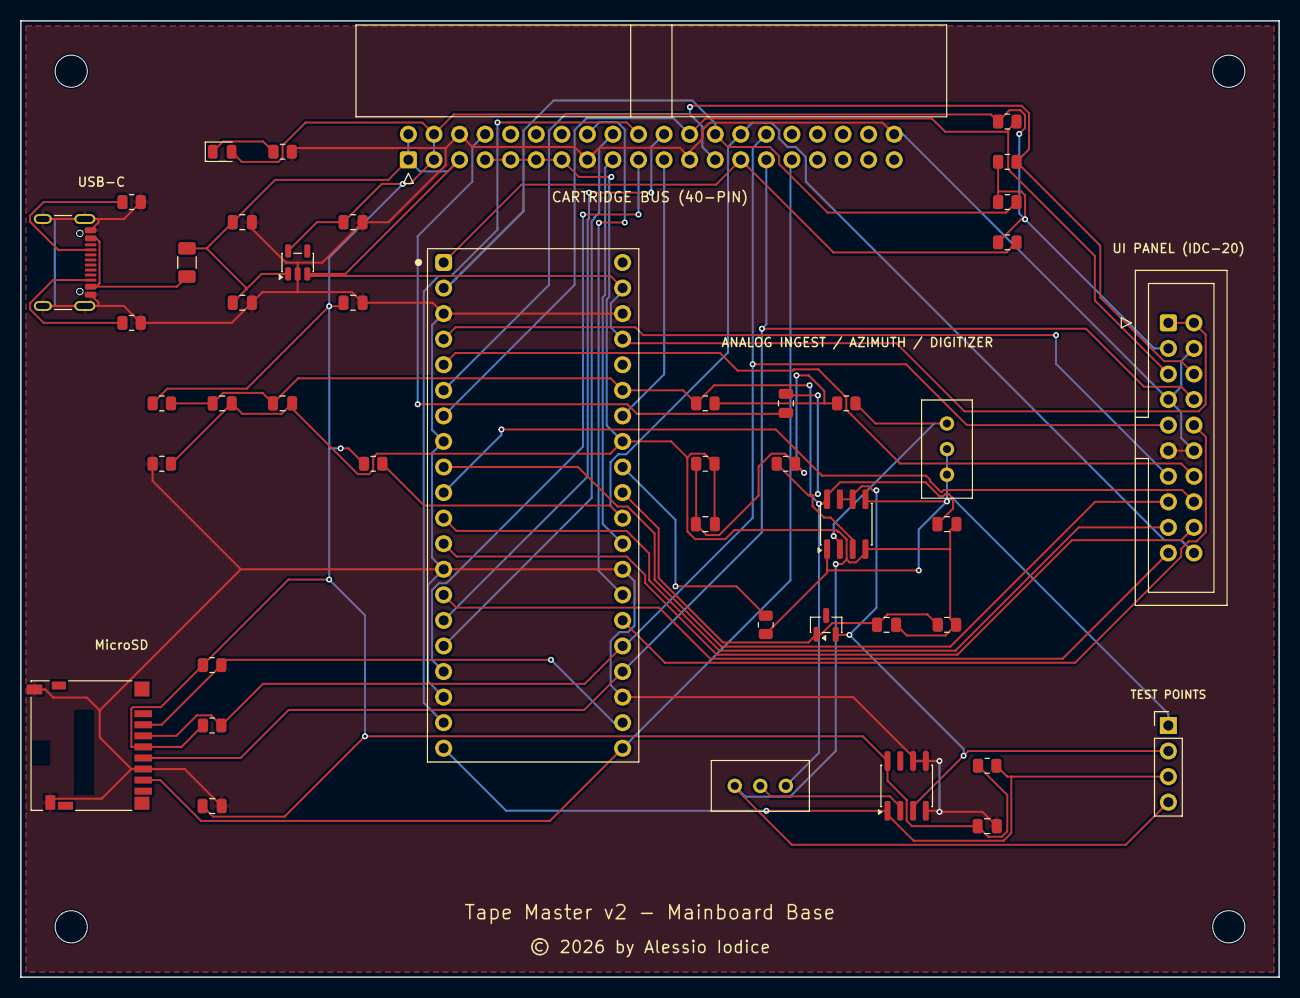
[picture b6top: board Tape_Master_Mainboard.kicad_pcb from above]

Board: 2 copper layers, 125.0 x 95.0 mm, 49 parts (0 on the bottom side), 43 nets.
